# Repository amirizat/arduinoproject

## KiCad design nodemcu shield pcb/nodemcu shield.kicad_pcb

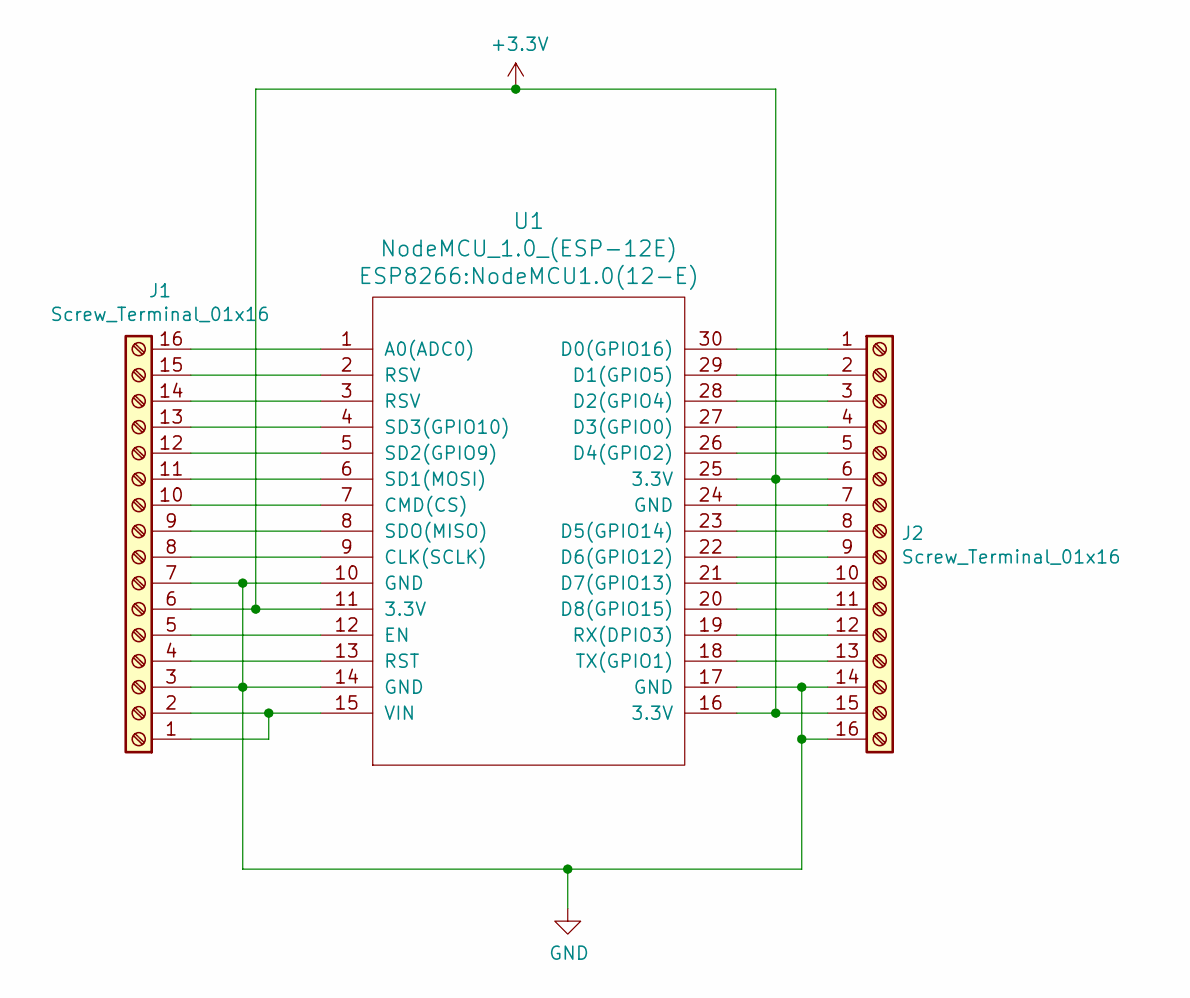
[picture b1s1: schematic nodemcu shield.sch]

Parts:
J1, J2: Screw_Terminal_01x16; TerminalBlock_WAGO_236-116_1x16_P5.00mm_45Degree
U1: NodeMCU_1.0_(ESP-12E); NodeMCU1.0(12-E)

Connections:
+3V3: J1.6, J2.6, J2.15, U1.11 (3.3V), U1.16 (3.3V), U1.25 (3.3V)
GND: J1.3, J1.7, J2.14, J2.16, U1.10 (GND), U1.14 (GND), U1.17 (GND)
unnamed: J1.1, J1.2, U1.15 (VIN)
unnamed: J1.4, U1.13 (RST)
unnamed: J1.5, U1.12 (EN)
unnamed: J1.8, U1.9 (CLK(SCLK))
unnamed: J1.9, U1.8 (SDO(MISO))
unnamed: J1.10, U1.7 (CMD(CS))
unnamed: J1.11, U1.6 (SD1(MOSI))
unnamed: J1.12, U1.5 (SD2(GPIO9))
unnamed: J1.13, U1.4 (SD3(GPIO10))
unnamed: J1.14, U1.3 (RSV)
unnamed: J1.15, U1.2 (RSV)
unnamed: J1.16, U1.1 (A0(ADC0))
unnamed: J2.1, U1.30 (D0(GPIO16))
unnamed: J2.2, U1.29 (D1(GPIO5))
unnamed: J2.3, U1.28 (D2(GPIO4))
unnamed: J2.4, U1.27 (D3(GPIO0))
unnamed: J2.5, U1.26 (D4(GPIO2))
unnamed: J2.7, U1.24 (GND)
unnamed: J2.8, U1.23 (D5(GPIO14))
unnamed: J2.9, U1.22 (D6(GPIO12))
unnamed: J2.10, U1.21 (D7(GPIO13))
unnamed: J2.11, U1.20 (D8(GPIO15))
unnamed: J2.12, U1.19 (RX(DPIO3))
unnamed: J2.13, U1.18 (TX(GPIO1))

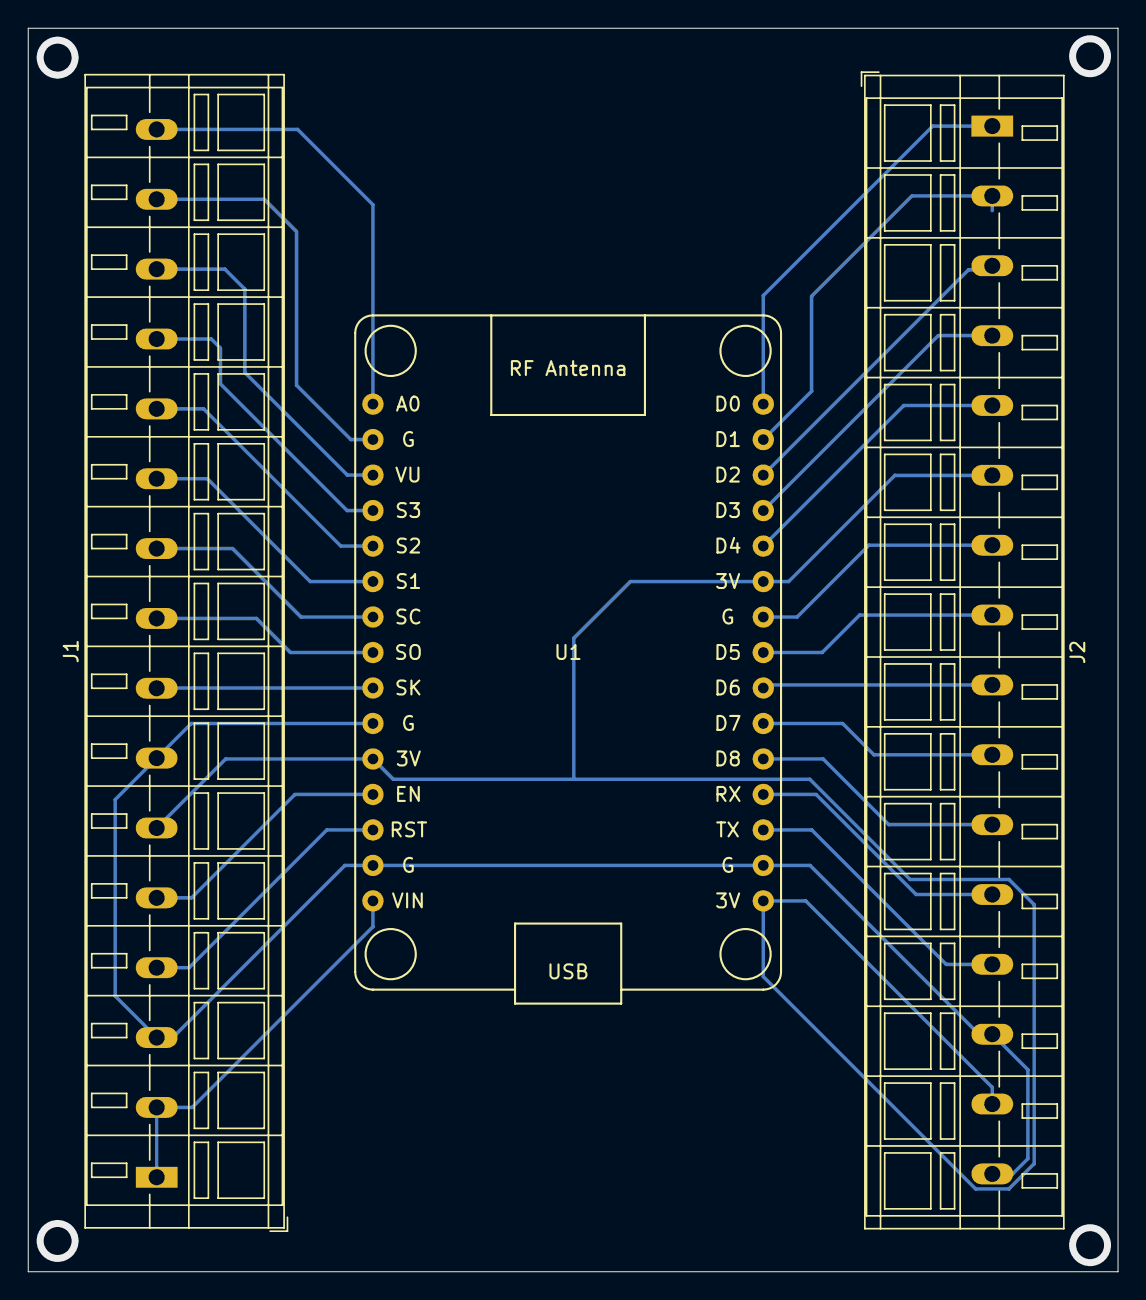
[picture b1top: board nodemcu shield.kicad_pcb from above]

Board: 2 copper layers, 78.0 x 89.0 mm, 3 parts (0 on the bottom side), 26 nets.
